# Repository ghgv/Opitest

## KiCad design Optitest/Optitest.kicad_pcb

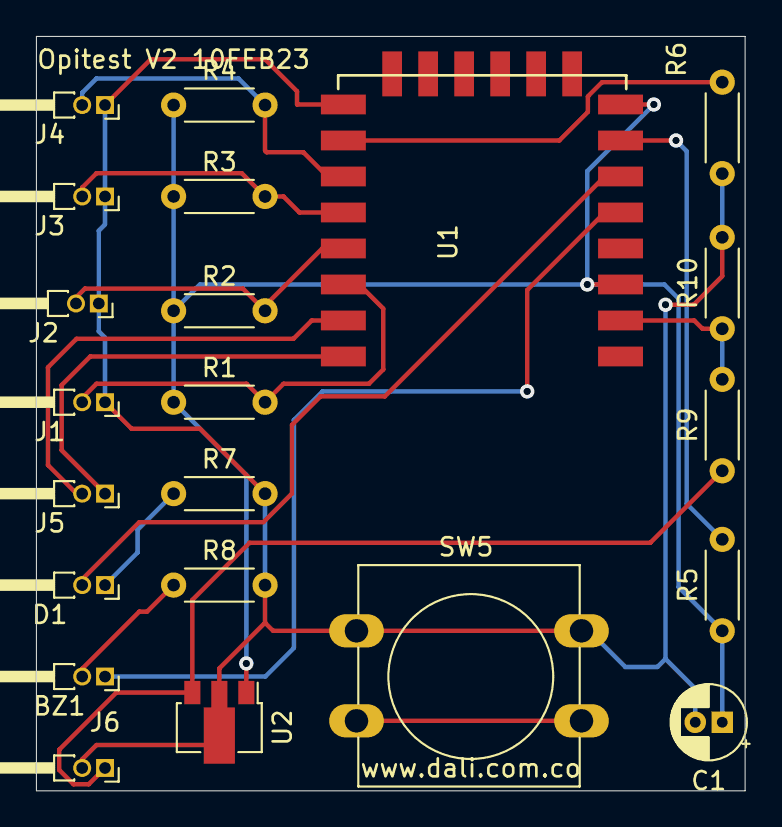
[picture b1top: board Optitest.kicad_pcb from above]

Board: 2 copper layers, 39.4 x 41.9 mm, 22 parts (0 on the bottom side), 16 nets.

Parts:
BZ1: Buzzer; PinHeader_2x01_P1.27mm_Horizontal
C1: 33uF; CP_Radial_D4.0mm_P1.50mm
D1: LED; PinHeader_2x01_P1.27mm_Horizontal
J1: Conn_MALO; PinHeader_2x01_P1.27mm_Horizontal
J2: Conn_REGULAR; PinHeader_2x01_P1.27mm_Horizontal
J3: Conn_BUENO; PinHeader_2x01_P1.27mm_Horizontal
J4: Conn_EXCELENTE; PinHeader_2x01_P1.27mm_Horizontal
J5: Programmer; PinHeader_2x01_P1.27mm_Horizontal
J6: Battery; PinHeader_2x01_P1.27mm_Horizontal
R1, R2, R3, R4, R5, R6: 1K; R_Axial_DIN0204_L3.6mm_D1.6mm_P5.08mm_Horizontal
R7, R8: 150; R_Axial_DIN0204_L3.6mm_D1.6mm_P5.08mm_Horizontal
R9, R10: R; R_Axial_DIN0204_L3.6mm_D1.6mm_P5.08mm_Horizontal
SW5: SW_CONF; SW_PUSH-12mm
U1: ESP-12E; ESP-12E_SMD
U2: L78L33_SOT89; SOT-89-3

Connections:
/BAT: J6.1, R9.1, U2.3
/BUENO: J3.2, R3.2, U1.12
/Buzzer_1: BZ1.1, U1.5
/CONF: R5.2, U1.7
/EXCELENTE: J4.2, R4.2, U1.11
/INF: D1.2, U1.6
/MALO: J1.2, R1.2, U1.14
/REGULAR: J2.2, R2.2, U1.13
/RXD: J5.2, U1.15
/TXD: J5.1, U1.16
/To_ADC_2: R9.2, R10.1, U1.2
/To_R5: R6.1, U1.10
GND: C1.2, J1.1, J2.1, J3.1, J4.1, J6.2, R6.2, R7.2, R8.2, R10.2, SW5.1, U1.9, U2.2
unnamed: BZ1.2, R8.1
unnamed: D1.1, R7.1
VCC: C1.1, R1.1, R2.1, R3.1, R4.1, R5.1, U1.3, U1.8, U2.1

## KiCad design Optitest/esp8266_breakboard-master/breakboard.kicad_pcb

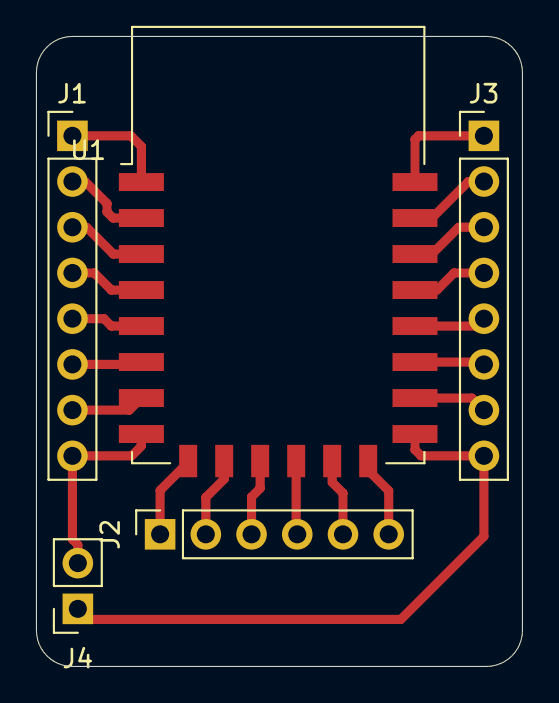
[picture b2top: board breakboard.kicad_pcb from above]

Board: 2 copper layers, 27.0 x 35.0 mm, 5 parts (0 on the bottom side), 22 nets.

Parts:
J1, J3: Conn_01x08_Male; PinHeader_1x08_P2.54mm_Vertical
J2: Conn_01x06_Male; PinSocket_1x06_P2.54mm_Vertical
J4: Conn_01x02_Male; PinSocket_1x02_P2.54mm_Vertical
U1: ESP8266-12E_ESP-12E; ESP-12E

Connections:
ADC: J1.2, U1.2
CS: J2.1, U1.9
EN: J1.3, U1.3
GND: J3.8, J4.1, U1.15
IO0: J3.5, U1.18
IO2: J3.6, U1.17
IO4: J3.4, U1.19
IO5: J3.3, U1.20
IO9: J2.3, U1.11
IO10: J2.4, U1.12
IO12: J1.6, U1.6
IO13: J1.7, U1.7
IO14: J1.5, U1.5
IO15: J3.7, U1.16
IO16: J1.4, U1.4
MISO: J2.2, U1.10
MOSI: J2.5, U1.13
RST: J1.1, U1.1
RX: J3.2, U1.21
SCLK: J2.6, U1.14
TX: J3.1, U1.22
VCC: J1.8, J4.2, U1.8

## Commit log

2023-02-11 Version2 10FEB23
2023-02-11 Opitest 11FEB23
